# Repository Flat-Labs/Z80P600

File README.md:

Z80P600
=======

A board and its firmware to replace (and enhance) the Z80 CPU of a SCI Prophet600.

Devised as a tribute to the amazing work of Gligli (http://gligli.github.io/p600fw/) and Imogen (https://github.com/image-et-son/p600fw),
it offers an alternative to Teensy board and its clones. 

Presets, settings, sequences and arpeggios are now stored on a separate F-RAM chip. Thus, all of these won't be lost during upgrades

The firmware functionalities are (almost) absolutely identical to the last Imogen's 2022 version, it only has been adapted to the new board. 
Please refer to the two above addresses for user manuals and informations.
I just added (Beta version) a misc command (From Tape + SEQ1) to wipe the settings out and set them to default . As tuning values are part of the settings, this obviously retunes the synth. 

Compiling and flashing the Firmware
===================================

Requirements:
- AVR-GCC toolchain
- avrdude uploader

For both these pieces of software on Windows, please refer to https://tinusaur.com/guides/avr-gcc-toolchain/.
A very clear and efficient guide to set up the toolchain. I used it with complete success on my windows box.

- python3 (https://www.python.org/downloads/)

- an USBASP programmer with six-pin header, such as this one (https://www.ebay.com/itm/116556456138) (Europe)
  or this one (https://www.ebay.com/itm/382191022734) (US)
  
Compiling:
----------
	> cd firmware
	> make

This will produce p600firmware.hex, which you can flash onto the board.

NOTE: As I'm not used to Github, I was unable to upload the dependence directory (.dep) in a correct manner. Therefore, there is a 'dep' directory in the firmare dir, that should be renamed to .dep for the make process to work.
Sorry for being a newbie here...

Flashing:
---------
1) For the first time.
	- Connect the Z80P600 board to the USBASP programmer (respect the 6-pins header pinout...)
	- Plug the USBASP into the PC
	- First, flash the fuses of the ATMEGA1281 (this has to be done only once, the first time):
	
		> avrdude -c usbasp -p m1281 -U lfuse:w:0x4f:m -U hfuse:w:0xdf:m -U efuse:w:0xf5:m -U lock:w:0xff:m
			
	- and flash the firmware:
	
		> avrdude -c usbasp -p m1281 -U flash:w:"p600firmware.hex":a
	
	To reflash a new version of firmware, only use the above avrdude command, as fuses have already been flashed.

	- Unplug the USBASP programmer of PC, disconnect the board, and plug it in the Z80 socket of P600
	- You're done ;)

2) Sysex upgrades 
	- Sysex upgrades work (From Tape + To Tape while powering on) and can be used to succesively upgrade the firmware through MIDI, provided that an older firmware has already been flashed once.

IMPORTANT NOTE : As the P600 presets, settings, sequences and arpeggios are now stored on a separate F-RAM, uploading (USBASP or sysex) a new firmware won't erase them.
Hence the option to reset the settings, just in case...

Board and PCB
=============

Schematics and PCB have been drawn using Kikad (V9 or above) : https://www.kicad.org/
The prototypes have been made (PCB + assembly) by JLC PCB, and the BOM file includes JLCPCB references for the parts.
The only part that is not included is the 40-pin DIL socket (Mouser ref. https://www.mouser.com/ProductDetail/437-1501064000106161 - gold plated, or https://www.mouser.com/ProductDetail/437-1508064000106101 - tinned), and it has to be hand-soldered.

Everything is working great, but the board LED seems a bit too bright for my taste...
So the R2 resitor value (for the LED) may be increased to something between 470 and 1000 ohms.

License
=======

Everything is under GPL v3 license, except files that have their own license in the header.

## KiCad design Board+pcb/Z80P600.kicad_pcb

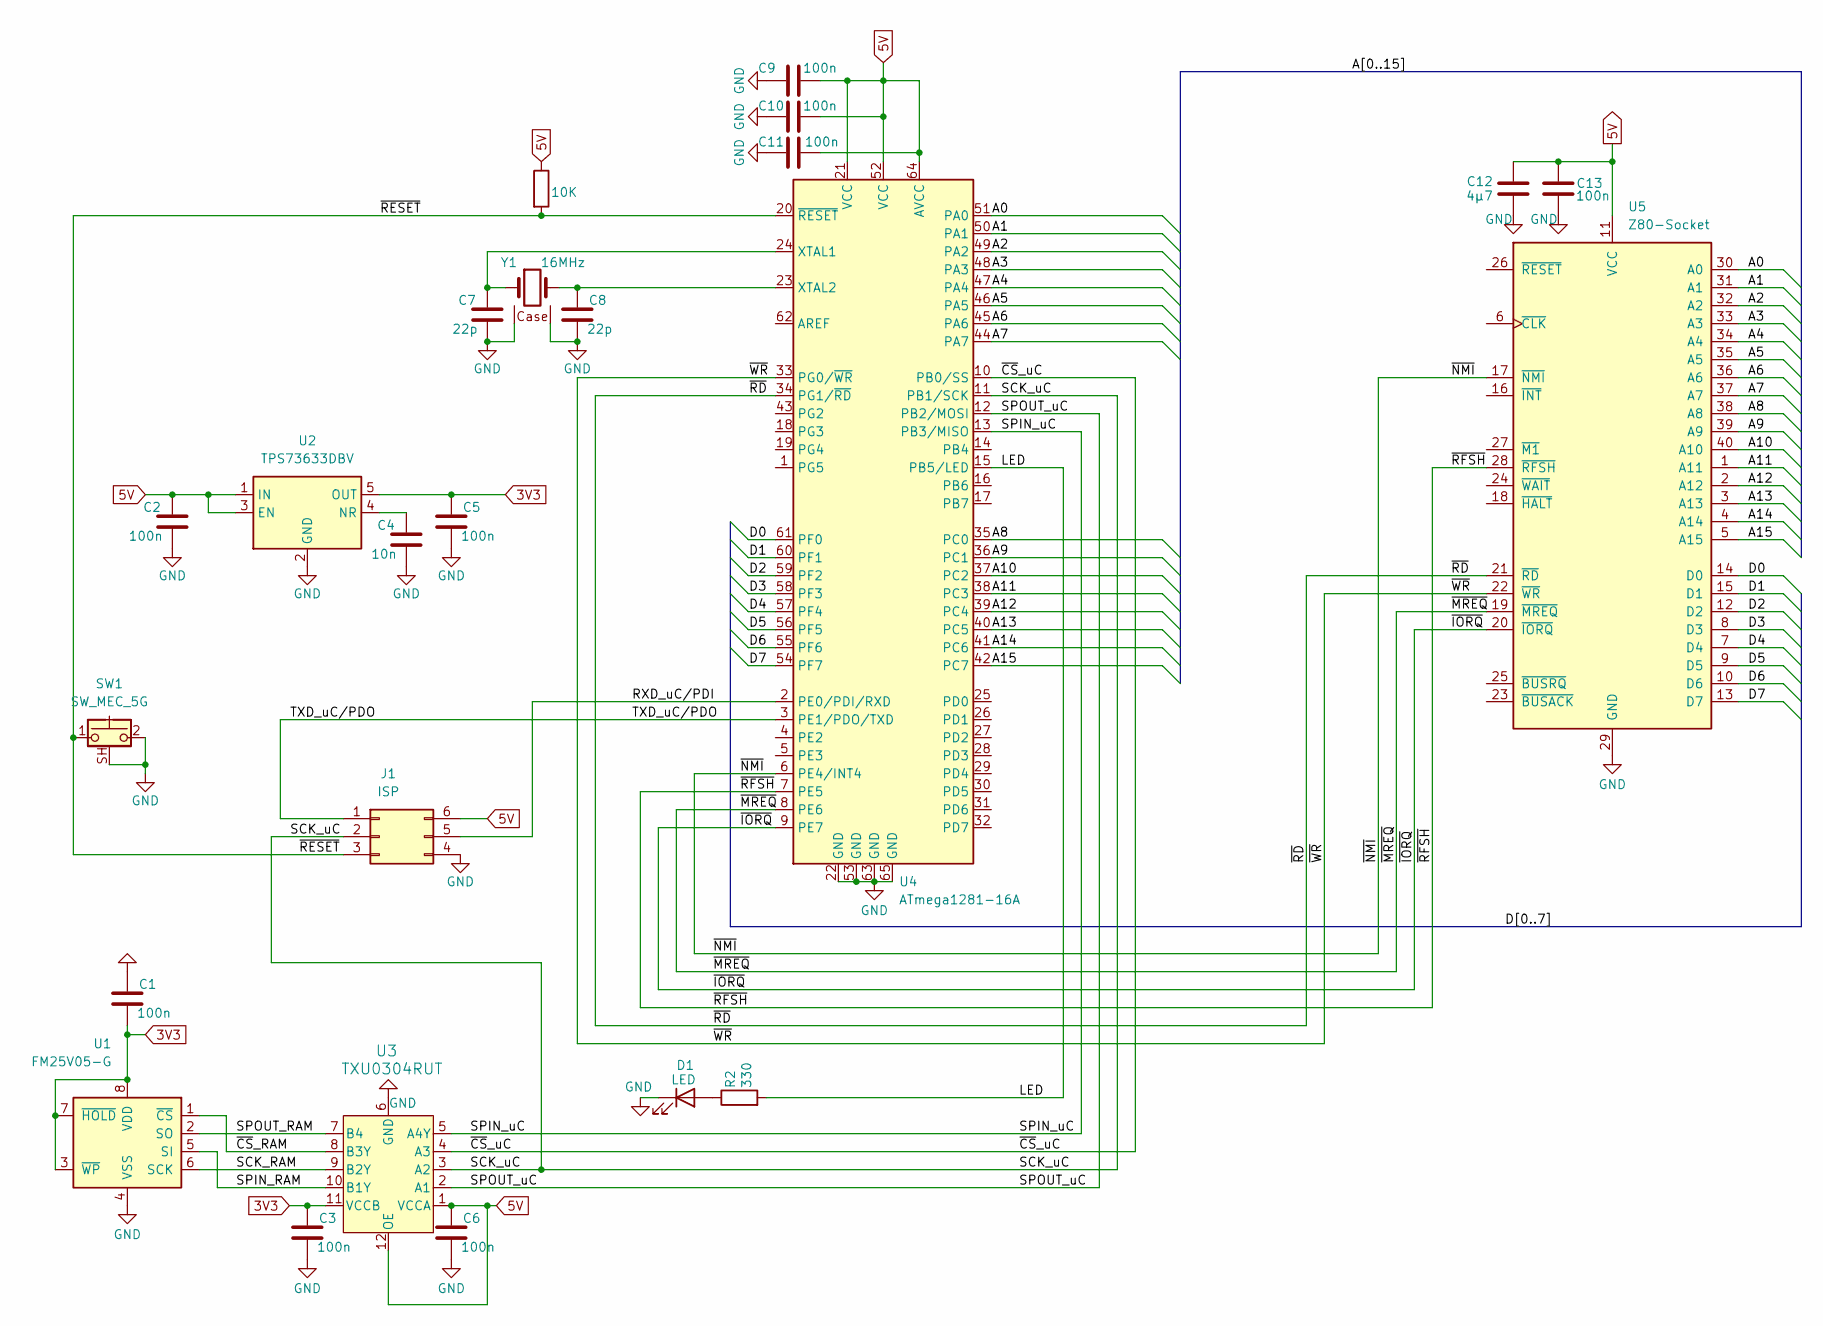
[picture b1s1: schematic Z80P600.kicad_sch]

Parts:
C1, C2, C3, C5, C6, C9, C10, C11, C13: 100n; C_0402_1005Metric
C4: 10n; C_0402_1005Metric
C7, C8: 22p; C_0402_1005Metric
C12: 4µ7; C_0805_2012Metric
D1: LED; LED_0603_1608Metric_Pad1.05x0.95mm_HandSolder
J1: ISP; PinHeader_2x03_P2.54mm_Vertical
R1: 10K; R_0402_1005Metric
R2: 330; R_0402_1005Metric
SW1: SW_MEC_5G; SW_Push_1P1T-SH_NO_CK_KMR2xxG
U1: FM25V05-G; SOIC-8_3.9x4.9mm_P1.27mm
U2: TPS73633DBV; SOT-23-5
U3: TXU0304RUT; Texas_R-PUQFN-N12
U4: ATmega1281-16A; QFN-64-1EP_9x9mm_P0.5mm_EP7.65x7.65mm_ThermalVias
U5: Z80-Socket; Z80_DIP-40_SMDSocket
Y1: 16MHz; Crystal_SMD_2520-4Pin_2.5x2.0mm

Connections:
3V3: C1.2, C3.1, C5.1, U1.3 (~WP), U1.7 (~HOLD), U1.8 (VDD), U2.5 (OUT), U3.11 (VCCB)
5V: C2.1, C6.1, C9.1, C10.1, C11.1, C12.1, C13.1, J1.6 (VCC), R1.1, U2.1 (IN), U2.3 (EN), U3.1 (VCCA), U3.12 (OE), U4.21 (VCC), U4.52 (VCC), U4.64 (AVCC), U5.11 (VCC)
/A0: U4.51 (PA0), U5.30 (A0)
/A1: U4.50 (PA1), U5.31 (A1)
/A2: U4.49 (PA2), U5.32 (A2)
/A3: U4.48 (PA3), U5.33 (A3)
/A4: U4.47 (PA4), U5.34 (A4)
/A5: U4.46 (PA5), U5.35 (A5)
/A6: U4.45 (PA6), U5.36 (A6)
/A7: U4.44 (PA7), U5.37 (A7)
/A8: U4.35 (PC0), U5.38 (A8)
/A9: U4.36 (PC1), U5.39 (A9)
/A10: U4.37 (PC2), U5.40 (A10)
/A11: U4.38 (PC3), U5.1 (A11)
/A12: U4.39 (PC4), U5.2 (A12)
/A13: U4.40 (PC5), U5.3 (A13)
/A14: U4.41 (PC6), U5.4 (A14)
/A15: U4.42 (PC7), U5.5 (A15)
/D0: U4.61 (PF0), U5.14 (D0)
/D1: U4.60 (PF1), U5.15 (D1)
/D2: U4.59 (PF2), U5.12 (D2)
/D3: U4.58 (PF3), U5.8 (D3)
/D4: U4.57 (PF4), U5.7 (D4)
/D5: U4.56 (PF5), U5.9 (D5)
/D6: U4.55 (PF6), U5.10 (D6)
/D7: U4.54 (PF7), U5.13 (D7)
/LED: R2.2, U4.15 (PB5/LED)
/RXD_uC/PDI: J1.5 (PDI), U4.2 (PE0/PDI/RXD)
/SCK_RAM: U1.6 (SCK), U3.9 (B2Y)
/SCK_uC: J1.2 (SCK), U3.3 (A2), U4.11 (PB1/SCK)
/SPIN_RAM: U1.5 (SI), U3.10 (B1Y)
/SPIN_uC: U3.5 (A4Y), U4.13 (PB3/MISO)
/SPOUT_RAM: U1.2 (SO), U3.7 (B4)
/SPOUT_uC: U3.2 (A1), U4.12 (PB2/MOSI)
/TXD_uC/PDO: J1.1 (PDO), U4.3 (PE1/PDO/TXD)
/~CS_RAM: U1.1 (~CS), U3.8 (B3Y)
/~CS_uC: U3.4 (A3), U4.10 (PB0/SS)
/~IORQ: U4.9 (PE7), U5.20 (~IORQ)
/~MREQ: U4.8 (PE6), U5.19 (~MREQ)
/~NMI: U4.6 (PE4/INT4), U5.17 (~NMI)
/~RD: U4.34 (PG1/~RD), U5.21 (~RD)
/~RESET: J1.3 (~RST), R1.2, SW1.1, U4.20 (~RESET)
/~RFSH: U4.7 (PE5), U5.28 (~RFSH)
/~WR: U4.33 (PG0/~WR), U5.22 (~WR)
GND: C1.1, C2.2, C3.2, C4.2, C5.2, C6.2, C7.2, C8.2, C9.2, C10.2, C11.2, C12.2, C13.2, D1.1 (K), J1.4 (GND), SW1.2, SW1.SH (B), U1.4 (VSS), U2.2 (GND), U3.6 (GND), U4.22 (GND), U4.53 (GND), U4.63 (GND), U4.65 (GND), U5.29 (GND), Y1.2 (Case), Y1.4 (Case)
unnamed: D1.2 (A), R2.1
unnamed: C4.1, U2.4 (NR)
unnamed: C7.1, U4.24 (XTAL1), Y1.1
unnamed: C8.1, U4.23 (XTAL2), Y1.3

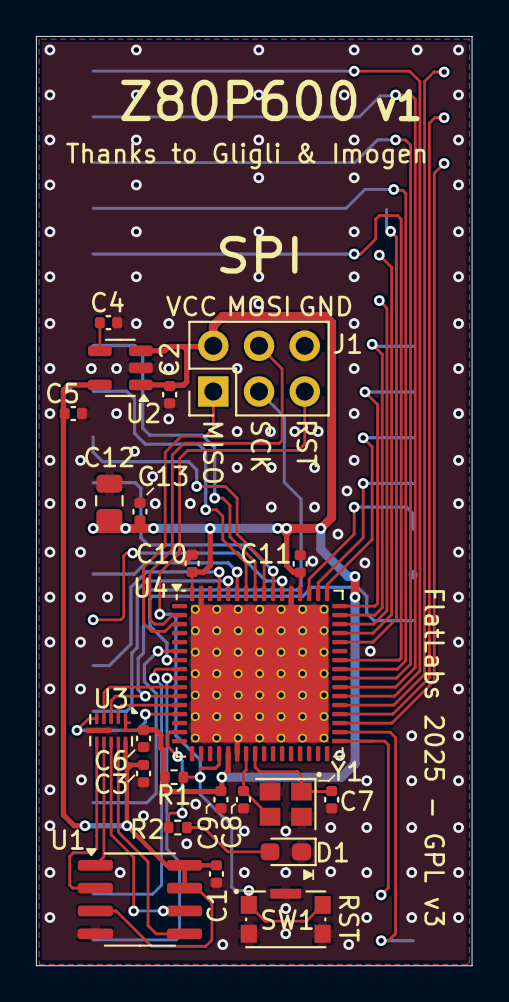
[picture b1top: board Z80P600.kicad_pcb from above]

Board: 2 copper layers, 24.2 x 51.6 mm, 24 parts (1 on the bottom side), 49 nets.

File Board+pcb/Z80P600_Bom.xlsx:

Reference | Qty | Value | DNP | Footprint
C1,C2,C3,C5,C6,C9,C10,C11,C13 | 9 | 100n |  | Capacitor_SMD:C_0402_1005Metric
C4 | 1 | 10n |  | Capacitor_SMD:C_0402_1005Metric
C7,C8 | 2 | 22p |  | Capacitor_SMD:C_0402_1005Metric
C12 | 1 | 4µ7 |  | Capacitor_SMD:C_0805_2012Metric
D1 | 1 | LED |  | LED_SMD:LED_0603_1608Metric_Pad1.05x0.95mm_HandSolder
J1 | 1 | ISP |  | Connector_PinHeader_2.54mm:PinHeader_2x03_P2.54mm_Vertical
R1 | 1 | 10K |  | Resistor_SMD:R_0402_1005Metric
R2 | 1 | 330 |  | Resistor_SMD:R_0402_1005Metric
SW1 | 1 | SW_MEC_5G |  | Button_Switch_SMD:SW_Push_1P1T-SH_NO_CK_KMR2xxG
U1 | 1 | FM25V05-G |  | Package_SO:SOIC-8_3.9x4.9mm_P1.27mm
U2 | 1 | TPS73633DBV |  | Package_TO_SOT_SMD:SOT-23-5
U3 | 1 | TXU0304RUT |  | Package_DFN_QFN:Texas_R-PUQFN-N12
U4 | 1 | ATmega1281-16A |  | Package_DFN_QFN:QFN-64-1EP_9x9mm_P0.5mm_EP7.65x7.65mm_ThermalVias
Y1 | 1 | 16MHz |  | Crystal:Crystal_SMD_2520-4Pin_2.5x2.0mm

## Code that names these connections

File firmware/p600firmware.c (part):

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#define CPU_125kHz      0x07
#define CPU_62kHz       0x08

#define MEMZONE		0		//	/MREQ = 0	/RFSH = 1	/IORQ = 1
#define IOZONE		1		//	/MREQ = 1	/RFSH = 0	/IORQ = 0

// Writes to synth hardware

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	LO_ADDR_PORT = (uint8_t)  (addr & 0x00FF); 			// Low byte on port A
		
 // /RFSH = 1 and /WR = 0 (to write the data)
	SIGNAL_PORT = SIGNAL_PORT | (1 << Z80_RFSH); // /RFSH = 1
	WR_PORT &= ~(1 << Z80_WR);  
}

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	HI_ADDR_PORT = (uint8_t) ((addr & 0xFF00) >> 8); 	// High byte on port C
	LO_ADDR_PORT = (uint8_t)  (addr & 0x00FF); 			// Low byte on port A

	SIGNAL_PORT = SIGNAL_PORT | (1 << Z80_RFSH); // /RFSH = 1
	WR_PORT &= ~(1 << Z80_RD);  				 // /RD to 0 (to read the data)

	CYCLE_WAIT(2);	//  Wait a bit
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
	CYCLE_WAIT(4);

//	while(PINC&0x10) // wait for NMI

	while (SIGNAL_PINS & (1 << Z80_NMI)) // wait for NMI
		CYCLE_WAIT(1);
	
	status = hardware_read(0, 0xe000); // read UART status
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
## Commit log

2026-01-28 Imogen original file
2026-01-28 FlatLabs version
2026-01-28 PCB files
2026-01-31 Easier make

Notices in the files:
Board+pcb/Z80P600.kicad_pcb:
FlatLabs 2025 - GPL v3
